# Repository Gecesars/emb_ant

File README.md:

# Painel setorial P1H · 5,09 a 5,25 GHz

**P2M19 R09 — simulações suspensas por solicitação do usuário em 14/11.** Referência RF preservada: R08, 14 passes, 20,544 dBi e ΔS 0,010484. Resumo enviado para gecesars@gmail.com. Planejamento da rede externa e montagem mecânica preliminar concluídos, com base de alumínio e dois conectores N. Falta de memória exige registro e parada sem repetição automática. [Estado, política e comunicação](projetos/P2M19/gestao_R09/README.md).

**P2M19 R08 — passes 13 e 14 concluídos em 14/11.** Malha preservada, colunas 72 mm, refletor 146 mm, 14 núcleos, 5,17 GHz, 16 entradas iguais/em fase e sem sweep. **ΔS final 0,010484 ≤0,05**; ganho frontal total **20,544 dBi**, aberturas **H 22,491° / V 3,783°**, máximos **+0,188° / +0,048°**. VSWR ativo **1,033–1,182**; maior VSWR com demais entradas casadas **1,316**. Entre os passes 13/14, ΔG **+0,0400 dB**, ΔH **−0,0986°**, ΔV **+0,0015°**; maior diferença de E/Emax **0,00353 H / 0,01006 V**. Balanço de potência consistente e zero reparos Major/Minor. O critério completo de 0,1 dB nas nove sondas por dois passes **ainda não foi atendido**; maior variação final 0,182 dB numa direção cerca de 31 dB abaixo do ganho frontal. Executados exatamente dois passes adicionais, sem novos cálculos programados. [Relatório, HFSS, VSWR e diagramas](projetos/P2M19/continuacao_72mm_ref146_14passes/README.md).

**P2M19 R07 — passes 11 e 12 concluídos em 14/11.** Malha preservada, colunas 72 mm, refletor 146 mm, 14 núcleos, 5,17 GHz, 16 entradas iguais/em fase e sem sweep. **ΔS final 0,014268 ≤0,05**; ganho frontal total **20,475 dBi**, aberturas **H 22,683° / V 3,778°**, máximos **+0,144° / +0,039°**. VSWR ativo **1,009–1,174**; maior VSWR com demais entradas casadas **1,301**. Entre os passes 11/12, ΔG **+0,0248 dB**, ΔH **−0,0634°**, ΔV **+0,0044°**. Balanço de potência consistente e zero reparos Major/Minor. A estabilidade completa de 0,1 dB nas nove sondas por dois passes **ainda não foi confirmada**; maior variação final 0,375 dB em uma direção cerca de 31 dB abaixo do ganho frontal. Executados exatamente dois passes adicionais, sem reiniciar a malha ou programar novos cálculos. [Relatório, HFSS, VSWR e diagramas](projetos/P2M19/continuacao_72mm_ref146_12passes/README.md).

**P2M19 R06 — convergência de ΔS confirmada em 14/11.** Executados somente os passes **9 e 10**, preservando os oito anteriores, colunas de 72 mm e refletor de 146 mm. 14 núcleos, 5,17 GHz, 16 entradas de 0,0625 W / 0°, sem sweep. ΔS **0,021617 / 0,024510**, dois passes consecutivos abaixo de 0,05. Ganho frontal total **20,391 dBi**, H/V **22,761° / 3,768°**, VSWR ativo **1,054–1,221** e máximo com demais entradas casadas **1,294**. Balanço de potência consistente e zero reparos Major/Minor. **A estabilidade completa dos campos ainda não foi confirmada**: ganho frontal variou +0,122 dB no último passe; maior variação entre as nove sondas foi 0,463 dB. Nenhum passe além de dez foi executado. [Resultados, HFSS e diagramas atualizados](projetos/P2M19/continuacao_72mm_ref146_10passes/README.md).

**P2M19 R05 — dois passes adicionais concluídos em 13/11, PRELIMINAR.** Preservados a geometria de colunas a 72 mm, refletor 146 mm e os seis passes anteriores; executados somente os passes 7/8, com 14 núcleos, 5,17 GHz, 16 entradas iguais/em fase, sem sweep. Resultado: **20,101 dBi**, H **22,734°**, V **3,753°**, VSWR ativo **1,143–1,353**. **ΔS=0,05196469 >0,05: não convergiu.** Balanço de potência consistente, zero reparos Major/Minor; ganho ainda variou +0,241 dB no último passe. O acompanhamento desta execução está concluído, sem novos passes programados. [Resultados, HFSS, comparação 6/8 e diagramas](projetos/P2M19/continuacao_72mm_ref146_8passes/README.md).

**P2M19 — comparação de 72/88 mm e três refletores concluída em 13/11, PRELIMINAR.** Executada fila local finita, com 14 núcleos, seis passes por geometria, entradas iguais/em fase, 5,17 GHz e sem sweep. Na comparação direta, mantendo refletor de 178 mm, colunas de 72 mm deram **19,209 dBi, H 24,238°, V 3,752°**, lóbulo horizontal **−4,866 dB** e ΔS **0,156138**. Os ajustes para refletores de 162/146 mm deram **19,418/19,500 dBi**, com H **23,989/23,550°**. **Nenhum caso convergiu ao alvo ΔS≤0,05 ou confirmou estabilidade dos campos; nenhum chegou a H=30°.** Balanços de potência consistentes, zero reparos Major/Minor, sem passes adicionais. A fila encerrou; não há agendamento recorrente. [Comparação, diagramas, nativos e evidências](projetos/P2M19/estudo_72mm/README.md) · [Operação da fila local](projetos/P2M19/automacao/README.md).

**P2M19 R01 — 16 níveis × duas colunas a 88 mm, estudo preliminar de 13/11.** Oito placas C12, 32 radiadores, dezesseis entradas de **0,0625 W / 0°**, 5,17 GHz, 14 núcleos e sem sweep. Encerrou no limite de **seis passes**, com **ΔS 0,177100 > 0,05: não convergiu**. Ganho frontal total **19,055 dBi**, abertura central H **19,428°**, V **3,820°**. Atinge 19 dBi numericamente, com margem de apenas 0,055 dB, sem validar a meta. Lóbulo horizontal em −37° a **−2,829 dB** do pico; VSWR ativo **1,364–2,295**. Balanço de potência consistente, zero reparos Major/Minor. Inclui perdas dos divisores impressos; exclui rede externa, cabos 3D e radome. [HFSS, CAD, diagramas, convergência e dados](projetos/P2M19/centro_16x2_88mm/README.md).

**P2S13 R17 — montagem DN100 dimensionada, preliminar (12/11).** Dois flanges Al Ø110 ×4,76 mm com canais **2,5 ×2,5 mm**, fixadores POM, dois N Amphenol082-6784 no flange inferior, chapa com linguetas e chicote completo. [FreeCAD, STEP, BOM, DXF e 12 páginas de documentação](projetos/P2S13/mecanica_R17/README.md). O teste sem abas resultou em **14,305 dBi, H78,77°, V10,11°, VSWR1,124/1,057**; ΔS0,030507 em seis passes, só um consecutivo válido. Abas pouco alteraram H; mantidas na montagem principal pelo vertical mais simétrico no resultado anterior. [Comparação HFSS/Nexxim e limites](projetos/P2S13/comparacao_refletor_R17/README.md). O fechamento mecânico completo ainda não foi qualificado em RF.

**P2S13 no tubo PVC — R16 concluída em 12/11 como estudo preliminar.** O ajuste `dn100_c02` atingiu **VSWR ativo 1,099 / 1,087** nas entradas do conjunto e **14,320 dBi** calculados em 5,17 GHz, com duas fontes iguais/em fase. Antena e divisor simulados separadamente; cabos somente no Nexxim, com perdas nominais. Tubo de catálogo **De 101,6 × parede 1,8 mm**, trecho aberto de 350 mm; propriedades dielétricas preliminares. Divisor convergiu em **6 passes / ΔS 0,017252**; antena encerrou em **6 / 0,041601**, sem os dois passes consecutivos exigidos e sem estabilidade completa de campos. Abertura agora informativa. **Não é qualificação do tubo comercial.** A sintonia melhora o conjunto carregado; isolado com saídas em 50 Ω, o divisor apresenta VSWR 2,154/2,153. [Pesquisa de tubos, explicação do VSWR, resultados e nativos](projetos/P2S13/tubo_pvc/README.md).

**Histórico anterior, sem tubo PVC:**

**P2S13 C09 ajustada — casamento do conjunto confirmado em 12/11.** Selecionada a c02: **VSWR ativo 1,184 / 1,226**, entradas de 0,5 W / 0° em 5,17 GHz; com a outra entrada casada, **1,142 / 1,207**. Seis ramais iguais de 19,323907 mm e PCB de 36 × 78 mm preservados, alterando apenas as duas seções dos transformadores. Divisor recalculado no HFSS: **5 passes, ΔS 0,020366, 14 núcleos**, sem radome, cabos 3D ou sweep. Nexxim efetivamente executado e conferido, erro S2 **6,15×10⁻¹⁶**. Com a antena S6 preservada, **14,146 dBi, H/V 86,241° / 10,068°, máximos 0° / +0,075°** permanecem preliminares pela estabilidade de campos da antena. O ajuste é para a carga da antena; o divisor isolado com saídas em 50 Ω tem VSWR 1,716/1,706. A abertura H≈100° e a qualificação completa continuam pendentes. [Relatório, dimensões, HFSS, Nexxim e FreeCAD](projetos/P2S13/casamento_c09/README.md). Montagem ajustada deixada aberta; nenhum novo Gerber liberado.

**Histórico C09 antes do ajuste:**

**P2S13 C09 compacto — Nexxim executado em 12/11, preliminar.** Novo divisor duplo 1:3 de **36 × 78 mm**, duas seções por ramal e comprimentos físicos/elétricos nominais iguais. HFSS separado para antena S6 e divisor S8, **sem radome e sem cabos longos em 3D**; seis coaxiais iguais de 134 mm representados por RLGC no Nexxim. Em 5,17 GHz, entradas de 0,5 W / 0°: **13,925 dBi** frontais, **VSWR 1,528 / 1,700**, H/V **86,228° / 10,073°**, máximos H/V **0° / +0,069°**. O casamento **não atende 1,25** e a abertura H está abaixo dos aproximadamente 100° buscados. Antena convergiu em **6 passes / ΔS 0,024379** e divisor em **5 / 0,019563**, todos com 14 núcleos; ainda há variação de campo de **0,309 dB** no último passe. A matriz Nexxim confere com cálculo independente, erro **4,61×10⁻¹⁶**. [Circuito nativo, diagramas, CAD e evidências](projetos/P2S13/compacto_c09/c00/README.md). Nenhum novo sweep; C08/Gerbers anteriores preservados, sem liberação C09 para fabricação.

**P2S13 R12 — continuação de oito passes e CAD/KiCad, 12/11.** Executados apenas passes 7 e 8 preservando a malha, 14 núcleos, 5,17 GHz, sem sweep e entradas 0,5 W / 0°. **ΔS 0,034291**, dois passes consecutivos ≤0,05: convergência S atendida. Ganho frontal **11,569 dBi**, VSWR ativo **1,547 / 1,455**, H/V **99,818° / 9,843°**, máximo V **−0,134°**; balanço de potência consistente. **Ganho frontal ≥12 dBi e VSWR ≤1,25 não atendidos; estabilidade de campo e simetria de 0,2 dB ainda pendentes** (assimetria V 0,208 dB). [Resultados, comparação e diagramas](projetos/P2S13/curvilinear_simplificado/continuacao8/README.md) · [KiCad/Gerbers: 3×M00 + 1×C08, DRC zero erros](projetos/P2S13/kicad/conjunto_R12/README.md) · [Montagem FreeCAD preliminar, deixada aberta](projetos/P2S13/mecanica_R12/README.md).

**Histórico P2S13 R12 — seis passes, 12/11, não validado.** Conjunto integral com C08, cabos e radome FR-4 de 2 mm; solver direto, elementos curvilíneos, 14 núcleos, duas entradas de 0,5 W / 0°. Em 5,17 GHz, seis passes: **ΔS 0,07831**, ganho frontal **11,572 dBi**, VSWR ativo **1,620 / 1,523**, H/V **98,902° / 9,796°**. O balanço de potência está consistente e o lóbulo principal vertical está praticamente centrado (**−0,008°**, assimetria **0,068 dB**). **Não atende à convergência, ao ganho frontal ≥12 dBi nem ao VSWR ≤1,25.** O pico horizontal é 12,724 dBi em +27,75°, distinto do ganho frontal. [Nativo, diagramas e auditoria R12](projetos/P2S13/curvilinear_simplificado/README.md).

**KiCad do divisor P2S13 C07 — 11/11:** [projeto, Gerbers e documentação](projetos/P2S13/kicad/divisor_duplo_1x3_C07/README.md), com a geometria nominal HFSS preservada. Conferência CAD/KiCad/CAM concluída; oito furos NPTH Ø0,9195 mm. **Fabricação padrão JLC ainda não liberada:** nove violações de folga mantidas porque o cobre chega aos furos e à borda. O ZIP inclui instruções de revisão especial; nenhum solve ou pedido de compra.

**P2S13 R09 — divisor corrigido e lóbulo principal vertical centrado nominalmente, 11/11.** Selecionada a C07, com compensação física nas trilhas e duas entradas de **0,5 W / 0°**. Em **5,17 GHz**, sem sweep: ganho frontal **12,746 dBi**, VSWR ativo **1,093/1,092**, aberturas H/V **98,614°/10,162°**, máximo vertical **−0,01°** na grade de 0,01° e assimetria máxima de **0,060 dB em ±4°**. Atende numericamente à meta atual de ≥12 dBi e à prioridade de centragem do lóbulo principal. O divisor convergiu em **seis passes**, **ΔS 0,023112**, dois consecutivos ≤0,05, **14 núcleos**, sem reparos Major/Minor; circuito conferido no Nexxim. Com a outra entrada casada, B fica em **1,255**, ligeiramente acima de 1,25. Resultado **preliminar**: permanecem as pendências de campos/reciprocidade da antena e não foi somada a radiação direta do divisor aos diagramas. [Relatório ilustrado, HFSS, FreeCAD, circuito e evidências](projetos/P2S13/divisor_duplo_1x3_correcao/README.md).

**Histórico R08, anterior à correção R09:**

**P2S13 — divisor duplo 1:3 físico simulado em 11/11.** A versão C01 concluiu seis passes, todos com 14 núcleos, em 5,17 GHz e sem sweep: **ΔS 0,049458**, dois passes consecutivos abaixo de 0,05. Conectada ao S6 da antena e conferida no Nexxim, com duas entradas de 0,5 W / 0°: **VSWR ativo 1,319/1,417**, ganho frontal **11,772 dBi**, H/V **99,308°/10,321°**. **Não atende VSWR≤1,25 nem ganho≥13 dBi.** O layout físico apresenta desequilíbrio de potência/fase nas saídas e não confirma o desempenho do plano de linhas anterior. Mantidas as ressalvas da antena e do modelo de componentes; nenhuma liberação para fabricação. [HFSS, circuito, CAD, diagramas e diagnóstico](projetos/P2S13/divisor_duplo_1x3_hfss/README.md).

**P2S13 — continuação de oito passes concluída em 11/11.** Três PCBs de dois elementos, dobra **28,5 mm / 150°**, mesma malha e geometria; somente passes 7 e 8 novos. Em 5,17 GHz, 14 núcleos, seis entradas iguais/em fase e sem sweep: **ΔS 0,017600**, ganho frontal **13,349 dBi**, H/V **98,727°/9,931°**, VSWR ativo máximo **1,3220**. Convergência S atendida; estabilidade de campos e reciprocidade estrita ainda pendentes. [Resultados e nativos](projetos/P2S13/continuacao_tres_placas2/README.md).

**Divisor duplo 1:3 — plano preliminar de circuito:** dois Wilkinson idênticos e ajuste comum de entrada resultam em VSWR máximo **1,1979** nas duas entradas, considerando fontes iguais/em fase e outra entrada casada. Ganho estimado **13,143 dBi**, H/V **98,720°/9,931°**; interconexão conferida no Nexxim. O divisor ainda não tem layout/validação EM, e os limites da malha da antena permanecem. [Plano, dimensões, dados e circuito](projetos/P2S13/divisor_duplo_1x3/README.md). [Histórico de seis passes](projetos/P2S13/tres_placas2/README.md) · [Campanha 4+2 interrompida](projetos/P2S13/dobras_placas_ajustadas/README.md).

**P2M21 R18 — mecânica PRELIMINAR concluída em 10/11:** [documentação, FreeCAD, chapa dobrada/planificada, BOM e imagens](projetos/P2M21/mecanica_preliminar_R18/README.md). Dez PCBs de quatro elementos, cinco por coluna: **20 níveis × 2 colunas**, passos **48/78 mm**, refletor de alumínio 2 mm, grampos de POM e dois N Amphenol 082-6784 a partir do STEP fornecido. Cabos de referência UT-141C. **Simulações interrompidas a pedido do usuário; nenhum solver será retomado automaticamente.** A rede externa de duas entradas para vinte conexões permanece pendente, assim como a liberação RF/mecânica. [Histórico R15/R16 e interrupção R17](projetos/P2M21/comparacao_colunas_niveis/README.md).

**P2M21, oito placas `4_elementos` — R14 de 10/11:** [conjunto 16×2, resultados e comparação](projetos/P2M21/oito_celulas_4_elementos/README.md), com passo horizontal aprovado de **72 mm** e folga de **2 mm**. Ensaio central com 16 portas iguais/em fase: **18,88 dBi**, H **25,25°**, V **3,75°** e VSWR ativo máximo **1,842**. **Ainda não validado: seis passes, ΔS 0,16430; requisito mantido em 0,05.** Nativos HFSS/FreeCAD, S16 e diagramas preservados, sem malhas no Git. Rede externa pendente da validação; sem sweep; a continuação posterior está registrada na R15.

**KiCad 4_elementos — 10/11:** [placa e documentação](projetos/P2M21/kicad/4_elementos/README.md) · [Gerbers para JLCPCB](projetos/P2M21/kicad/4_elementos/4_elementos_gerbers_JLCPCB.zip). Geometria R13 C12 preservada, 70 × 184 mm, RO4350B de núcleo 0,76 mm, dois divisores 1:4; DRC sem erros ou desconexões. O apontamento H +0,75° ainda excede a tolerância atual de ±0,5°; V −0,25° atende.

**P2M21 — módulo de quatro elementos, R13 de 10/11:** casamento numérico **VSWR ≤1,25 em 5,09–5,25 GHz**, com Fast de 161 pontos e conferências discretas. Pior VSWR ativo **1,23548**, outra entrada casada **1,23260**. Em 5,17 GHz: **12,4566 dBi**, H **72,055°**, V **15,183°**; máximos **+0,75°/−0,25°**, mantendo a ressalva de apontamento horizontal. Seis passes, ΔS **1,672%**, 14 núcleos, entradas iguais/em fase e cabos físicos com perdas. [Relatório, curvas, dimensões e nativos](projetos/P2M21/quatro_elementos_casamento_banda/README.md). A aprovação do casamento deste módulo não qualifica o painel completo de 21 dBi.

**P1H semipronta — campanha R07 suspensa a pedido do usuário em 8/11.** A R06 permanece qualificada somente em 5,17 GHz. O centro R07 foi conferido; a varredura de 17 frequências foi interrompida voluntariamente para iniciar o novo projeto. Não há aprovação de banda R07. [Registro do congelamento](resultados/r07/estado_semipronta.json).

**Continuação central P2M21 concluída:** dois passes adicionais, seis no total, em 5,17 GHz; 14 núcleos nos passes finais. Ganho total **23,32 dBi**, H **32,54°**, V **3,48°**. **Preliminar: ΔS 0,110424, sem convergência e com reprovações numéricas.** Sem sweep. [Comparação e diagramas polares E/Emax](projetos/P2M21/centro_sem_refinamento/continuacao_6_passes/README.md) · [Histórico de quatro passes](projetos/P2M21/centro_sem_refinamento/README.md).

**Novo projeto P2M21:** duas colunas, 16 níveis e duas entradas MIMO independentes, com meta de **21 dBi por entrada em 5,09–5,25 GHz**, a outra entrada casada em 50 Ω. [Concepção, placas KiCad, montagem FreeCAD e HFSS separado](projetos/P2M21/README.md).

**R06 qualificada numericamente em 5,17 GHz:** PCB contínua de dez elementos com divisores compactos, duas entradas de 0,5 W a 0°, cabos ideais sem atenuação. Resultado final: **17,3593 dBi, H 96,0643°, V 5,6158°**, VSWR ativo A/B **1,2115 / 1,1292** e com a outra entrada casada **1,2321 / 1,2474**. Convergência de 23 passes, estabilidade de malha aprovada e circuito conferido no Nexxim. [Relatório ilustrado de 15 páginas](resultados/r06/P1H_R06_Relatorio.pdf) · [Resultados e limites](resultados/r06/README.md) · [Cotação JLCPCB](resultados/r06/cotacao.md) · [Montagem e chapa R06](freecad/mecanica_R06/README.md). O aceite é somente no centro da banda, sem perdas dos cabos e com conectores N ideais. Os resultados reprovados abaixo são históricos, sob o método anterior.

**Histórico R02 — cálculo integrado anterior.** As duas montagens com divisores compactos reprovam o requisito conjunto de abertura horizontal e ganho em toda a banda. A 5,17 GHz, a placa contínua produziu **94,82° / 5,54° / 12,00 dBi** e as dez placas individuais **105,13° / 5,57° / 13,48 dBi**, respectivamente em H, V e ganho frontal realizado. A compacta teve a menor perda de distribuição entre as arquiteturas estudadas. [Comparação dos painéis](resultados/r02/comparacao_paineis.md) · [Relatório de engenharia](resultados/r02/Relatorio_P1H.pdf) · [Quatro materiais e divisores alongados](resultados/r03/README.md)

Projeto de uma coluna de dez antenas impressas com duas polarizações e passo de 52,6 mm no eixo X. A comparação atual usa duas PCBs distribuidoras, uma para os cinco radiadores inferiores e outra para os cinco superiores. Cada PCB atende às duas polarizações. A referência de ganho é a potência incidente nas duas entradas N, com 0,5 W a 0° em cada uma. Os modelos anteriores com divisor único e ramais de 254 mm também estão preservados.

| Para consultar | Arquivos |
|---|---|
| Modelos HFSS das duas montagens | [Uma placa](hfss/antenas/P1H_Continua.aedt) · [Dez placas](hfss/antenas/P1H_Separadas.aedt) · [Elemento de origem](hfss/antenas/P1H_AB_em_fase.aedt) |
| Modelos HFSS da alimentação | [Divisor de 22 portas](hfss/alimentacao/Divisor_2x10_PTFE.aedt) · [Transição soldada](hfss/alimentacao/Junta_UT141_P1H.aedt) |
| Fontes KiCad | [Coluna contínua](kicad/P1H_Coluna_10) · [Radiador individual](kicad/P1H_Individual) · [Divisor duplo](kicad/Divisor_2x10) |
| Referências dimensionais FreeCAD | [Uma placa](freecad/P1H_10_Continua.FCStd) · [Dez placas](freecad/P1H_10_Separadas.FCStd) · [Envelope do divisor](freecad/Divisor_2x10_PTFE.FCStd) |
| Mecânica do protótipo com refletor contínuo | [Montagem, chapa dobrada, planificação e desenho de fabricação](freecad/mecanica_R01/README.md) |
| Painel integrado R01 | [Modelo HFSS com duas portas N](hfss/antenas/P1H_R01.aedt) · [Premissas e reprodução](automacao/r01/README.md) · [Cotação da placa contínua e do divisor](resultados/r01/cotacao.md) |
| R02 com divisores inferior e superior | [Montagem, chapa e chicote](freecad/mecanica_R02/README.md) · [HFSS integrado](hfss/antenas/P1H_R02.aedt) · [Reprodução](automacao/r02/README.md) · [Cotação das três placas](resultados/r02/cotacao.md) |
| Controle R02-S com as dez placas individuais | [HFSS no mesmo refletor e rede R02](hfss/antenas/P1H_R02_10Separadas.aedt) · [Comparação convergida dos painéis](resultados/r02/comparacao_paineis.md) · [Comparação dos divisores em 50 Ω](resultados/r02/rede/README.md) · [Relatório de engenharia](resultados/r02/Relatorio_P1H.pdf) |
| R03 com saídas alinhadas e dois divisores alongados | [Comparação com a compacta e quatro laminados](resultados/r03/README.md) · [Montagem e chapa](freecad/mecanica_R03/README.md) · [HFSS do painel completo](hfss/antenas/P1H_R03_Alongada.aedt) · [Cotação](resultados/r03/cotacao.md) |
| Fabricação | [Pacotes Gerber com furação das revisões](fabricacao/gerbers) · [Ligação dos cabos da versão inicial](fabricacao/montagem/ligacao_dos_cabos.csv) · [Cotação JLCPCB inicial](fabricacao/cotacao/Cotacao_JLCPCB.md) |
| Estudos anteriores | [Colunas de 8, 9 e 10 elementos](documentacao/historico/comparacao_colunas.md) · [Elemento com ambas as portas em fase](documentacao/historico/analise_AB.md) · [Dados numéricos](resultados/historico) |
| Como reproduzir | [Procedimento e convenções](automacao/README.md) |

Os **critérios atuais de RF da R06** são abertura horizontal a −3 dB entre 81° e 99° (alvo 90°), VSWR < 1,5 nas duas entradas e ganho realizado frontal ≥ 16 dBi em +Z, no centro de 5,17 GHz e sem perdas dos cabos. A abertura vertical pode ser menor que 7°. A banda de interesse continua 5,09–5,25 GHz; os 17 pontos dos divisores não demonstram por si só desempenho do painel em toda a banda. As reprovações dos painéis integrais anteriores permanecem como histórico.

O ensaio anterior das duas revisões de PCB com refletores individuais foi interrompido após a convergência da placa contínua no centro da banda. O ganho mínimo de 16,58 dBi do estudo histórico corresponde às antenas individuais antes dos ajustes dos pads e furos. As campanhas R01, R02 e R02-S usam a mecânica completa, incluindo o refletor dobrado e os conectores N. [Estudo histórico](documentacao/historico/comparacao_colunas.md)

No painel completo R01, o ponto convergido de 5,17 GHz apresentou 14,06 dBi de ganho frontal e aberturas de 102,34° na horizontal e 6,19° na vertical. A R01 reprova as metas simultâneas de banda. [Campos, convergência e métricas](resultados/r01/README.md)

Os **radiadores** usam RO4350B de 0,76 mm (Dk de projeto 3,66). Os divisores de referência usam PTFE ZYF300CA-C de 1,52 mm. São espessuras do laminado. A placa longa mede 501,7125 × 28,3125 mm e a individual mede 28,3125 × 28,3125 mm. Os modelos RF anteriores usam dez refletores individuais de 48,3125 × 36 mm. Os protótipos mecânicos R01 a R03 usam refletor contínuo dobrado de alumínio de 2 mm, apoios em poliacetal e conectores N com junta de vedação. Os modelos históricos de cobre excluíam a camada de níquel-fósforo; a R06 inclui ENIG nominal sobre cobre físico de 35 µm.

Os modelos HFSS nativos podem gerar a malha novamente. O Git guarda projetos, dados de engenharia e documentos. As malhas, os campos volumétricos, os backups e os arquivos temporários ficam nos diretórios locais de trabalho. Os Gerbers em **fabricacao/gerbers** correspondem aos protótipos cotados. As campanhas integrais anteriores reprovam suas metas; a R06 atende ao aceite de centro pelo método separado solicitado, conforme o relatório final.

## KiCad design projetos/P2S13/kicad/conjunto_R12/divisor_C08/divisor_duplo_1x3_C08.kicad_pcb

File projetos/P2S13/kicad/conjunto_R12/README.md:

# Conjunto R12 no KiCad — três placas M00 e divisor C08

Pacote de 12/11/2026 com **três placas radiantes idênticas de dois elementos M00** e **um divisor duplo 1:3 C08**. São quatro PCBs, seis elementos radiantes e seis interligações coaxiais de 50 mm. As duas entradas externas pertencem à C08; cada polarização alimenta uma das entradas das três M00.

**Geometria nominal simulada preservada. A qualificação RF é separada e este pacote não libera produção.** A R12 com radome está em verificação de convergência; consultar [resultados R12](../../curvilinear_simplificado/README.md) e sua continuação. Não foi alterado cobre para corrigir casamento, DRC ou adaptação de processo.

| PCB | Quantidade por antena | Arquivo editável | Gerbers |
| --- | ---: | --- | --- |
| Radiante M00, dois elementos e dois divisores 1:2 | 3 | [2_elementos.kicad_pro](placa2_M00/2_elementos.kicad_pro), [PCB](placa2_M00/2_elementos.kicad_pcb) | [M00 — para revisão RF/processo](placa2_M00/M00_Gerbers_PARA_REVISAO_RF.zip) |
| Divisor duplo 1:3 C08 | 1 | [divisor_duplo_1x3_C08.kicad_pro](divisor_C08/divisor_duplo_1x3_C08.kicad_pro), [PCB](divisor_C08/divisor_duplo_1x3_C08.kicad_pcb) | [C08 — pacote original preservado](divisor_C08/C08_Gerbers_PARA_REVISAO_RF.zip) |

A M00 foi criada agora no KiCad 10.0.5 a partir da arte exata usada no HFSS. A placa antiga `projetos/P2M21/kicad/2_elementos` é uma versão v05 diferente e foi preservada. A C08 já existia e foi reutilizada byte a byte, incluindo suas conferências; não houve redesenho.

## Especificações nominais

| Item | M00 | C08 |
| --- | --- | --- |
| Dimensões | 50 × 88 mm | 220 × 64 mm |
| Núcleo dielétrico | RO4350B, 0,76 mm | ZYF300CA-C, 1,52 mm |
| Valores usados no HFSS | εr 3,66; tanδ 0,0037 | εr 2,94; tanδ 0,0016 |
| Cobre externo | 35 µm por face | 35 µm por face |
| Espessura geométrica núcleo+cobre | 0,83 mm, antes do acabamento | 1,59 mm, antes do acabamento |
| Acabamento | ENIG nominal, sem máscara e sem serigrafia | ENIG nominal, sem máscara e sem serigrafia |
| Furos acabados por placa | 4 vias Ø0,40 mm + 2 entradas Ø1,10 mm, todos PTH | 8 entradas/saídas Ø1,10 mm, todos PTH |
| Diâmetro nominal das ilhas | Vias Ø0,726 mm; pads PTH Ø1,60 mm, com cobre superior de entrada Ø1,90 mm incorporado à arte | Ø1,80 mm |
| Metalização de parede no modelo RF | **35 µm** | **18 µm** |
| NPTH / componentes SMD | Nenhum | Nenhum |

O acabamento ENIG do modelo usa Au 0,0254 µm e NiP 4,5 µm nominal. As espessuras de parede dos PTH foram lidas dos sólidos do CAD; não são suposições do exportador KiCad. Em especial, **não substituir os 35 µm de metalização da M00 pelos 18 µm da C08 sem revisão de engenharia**. As notas preservam o modelo, mas disponibilidade, tolerâncias finais e stackup precisam ser confirmados com o fabricante antes da compra. Não houve cotação ou pedido nesta entrega.

Na M00, o passo dos elementos é 48 mm; transformadores de sinal medem 0,546717 mm de largura × 13,151813 mm de comprimento. O sinal de 50 Ω tem largura 1,623415 mm. As entradas ficam em HFSS X=2,509168413 mm, Y=−18 mm (A) e +18 mm (B). Os planos de retorno e divisores acrescentados são simétricos, mantendo as transições dos radiadores originais.

## Conferências

- M00: **zero erros DRC e zero itens desconectados**. Os 138 avisos são de pontes de máscara porque a abertura cobre toda a PCB; não há exclusões DRC para ocultá-los.
- C08: DRC repetido em 12/11, **zero erros e zero desconectados**, com 113 avisos do mesmo tipo. Todos os 18 arquivos originais do pacote foram comparados por SHA-256.
- Cobre KiCad M00 comparado à arte efetiva, incluindo anilhas, pads e furos: desvio máximo de 0,000001 mm nas bordas. Conferência independente com as 14 faces de cobre do CAD FreeCAD usado na R12: tolerância de 0,000005 mm, dez grupos camada/rede.
- Gerbers X2 e Excellon realmente exportados foram relidos e comparados. Contorno fechado, máscara integral, cobre e furação corretos. Furação em formato 3:6 mm, resolução nominal 0,000001 mm; erro máximo de arredondamento XY de 0,000000878 mm. Esses números são precisão digital de exportação, **não tolerâncias de fabricação**.
- Continuidade das redes SIG_A, SIG_B, RET_A e RET_B verificada, sem curto entre redes. Folga mínima entre redes da M00: 0,188750 mm; cobre a 4 mm da borda.

Evidências: [conferência CAD do conjunto](conferencia_CAD_conjunto.json), [M00 KiCad](placa2_M00/verificacao.json), [M00 CAM](placa2_M00/verificacao_gerbers.json), [C08](divisor_C08/verificacao.json), [origem C08](origem_C08.json) e [manifesto](manifesto.json).

## Montagem e reprodução

Centros das três placas radiantes no conjunto: X=−96, 0 e +96 mm. Entre bordas há 8 mm de vão. Divisor C08 com giro de 180° em X e translação Z=−35,231 mm conforme a configuração HFSS; não espelhar Gerbers para obter essa orientação de montagem. Ver [lista de placas](lista_placas.csv) e [interligações](interligacoes.csv).

Os projetos contêm objetos KiCad editáveis: polígonos de cobre associados a redes, pads PTH, vias, contorno e stackup. Não foram criados componentes fictícios nem um esquema lumped para substituir a geometria distribuída RF. Identificações estão em F.Fab e não são enviadas como serigrafia. Não há BOM/CPL de montagem automática; os cabos são soldados manualmente.

Os scripts `r12_kicad_preparar.py`, `r12_kicad_placa2.py`, `r12_kicad_furacao.py`, `r12_kicad_conferir.py`, `r12_kicad_gerbers.py`, `r12_kicad_faces_cad.py` e `r12_kicad_validar_cad.py` em `projetos/P2S13/automacao` reproduzem geração e auditoria sem executar HFSS. Preservar os arquivos-fonte, as notas de fabricação e a revisão antes de regenerar o pacote.

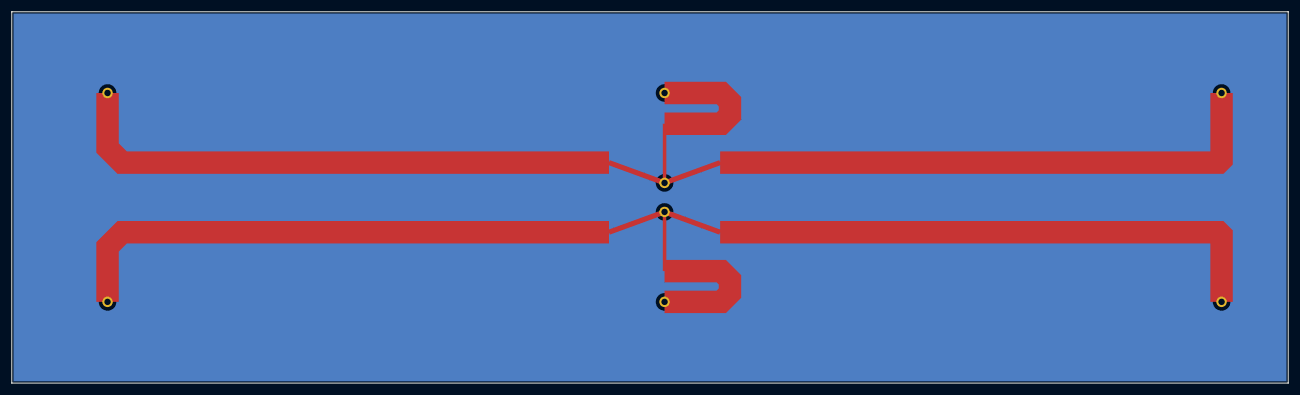
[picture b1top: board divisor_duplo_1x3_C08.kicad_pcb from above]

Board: 2 copper layers, 220.0 x 64.0 mm, 8 parts (0 on the bottom side), 3 nets, no tracks yet.

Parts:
J1: IN_A_COAX_SOLDADO
J2: R1_A_COAX_SOLDADO
J3: R2_A_COAX_SOLDADO
J4: R3_A_COAX_SOLDADO
J5: IN_B_COAX_SOLDADO
J6: R1_B_COAX_SOLDADO
J7: R2_B_COAX_SOLDADO
J8: R3_B_COAX_SOLDADO

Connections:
GND: J1.2, J2.2, J3.2, J4.2, J5.2, J6.2, J7.2, J8.2
SIG_A: J1.1, J2.1, J3.1, J4.1
SIG_B: J5.1, J6.1, J7.1, J8.1

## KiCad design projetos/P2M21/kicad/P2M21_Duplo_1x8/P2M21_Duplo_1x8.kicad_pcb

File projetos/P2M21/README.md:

# P2M21 — duas colunas, MIMO 2×2, meta de 21 dBi por entrada

**P2M21 R18 — mecânica PRELIMINAR concluída em 10/11:** [documentação, FreeCAD, chapa dobrada/planificada, BOM e imagens](mecanica_preliminar_R18/README.md). Dez PCBs de quatro elementos, cinco por coluna: **20 níveis × 2 colunas**, passos **48/78 mm**, refletor de alumínio 2 mm, grampos de POM e dois N Amphenol 082-6784 a partir do STEP fornecido. Cabos de referência UT-141C. **Simulações interrompidas a pedido do usuário; nenhum solver será retomado automaticamente.** A rede externa de duas entradas para vinte conexões permanece pendente, assim como a liberação RF/mecânica. [Histórico R15/R16 e interrupção R17](comparacao_colunas_niveis/README.md).

**Painel de oito células — R14 de 10/11:** [montagem HFSS/FreeCAD, diagramas e comparação](oito_celulas_4_elementos/README.md). Oito cópias de `4_elementos`, em quatro placas verticais × duas colunas, totalizam 16 níveis × 2 radiadores. Passos de **48 mm vertical / 72 mm horizontal**, com **2 mm de folga lateral**. Em 5,17 GHz, 16 portas de 0,0625 W/0°, 1 W total: **18,8776 dBi**, H **25,2549°**, V **3,7541°**, máximos **−1,25° / 0°**, VSWR ativo máximo **1,8421** e com demais portas casadas **1,4125**. **Não validado: seis passes, ΔS 0,164297, acima do alvo 0,05**, e campos ainda variando. Malha sem reparos Major/Minor; passividade, reciprocidade e recomposição dos campos conferidas. Mantidos 14 núcleos, sem GUI e sem sweep; inclui os cabos físicos de 50 mm das células. O painel individual R04 também não convergiu e tem outros espaçamentos, portanto a comparação é histórica. A rede externa de duas entradas para 16 conexões aguarda validação dos diagramas; o estado de seis passes é histórico; os dois passes adicionais autorizados estão registrados na R15.

**KiCad em 10/11 — [4_elementos](kicad/4_elementos/README.md):** criada a placa de **70 × 184 mm**, com passo de **48 mm** e dois divisores 1:4, preservando a geometria R13 C12. [Gerbers/Excellon para JLCPCB](kicad/4_elementos/4_elementos_gerbers_JLCPCB.zip), RO4350B de núcleo 0,76 mm. Cobre, contorno e dez furos conferidos; **DRC sem erros ou desconexões**. A tolerância atual é **±0,5° em H e V**: a C12 mantém H +0,75° (fora) e V −0,25° (dentro). Esta conversão não altera a geometria nem inicia nova simulação.

**Módulo de quatro elementos — R13 concluída em 10/11:** a meta de **VSWR ≤1,25** foi atendida numericamente na banda de **5,09–5,25 GHz**. O Fast tem 161 pontos de saída e foi conferido por soluções discretas em 5,09/5,17/5,25 GHz e no pior ponto, **5,173 GHz**. Máximo ativo confirmado: **1,23548**; com a outra entrada em 50 Ω: **1,23260**. O ajuste usa três seções nos transformadores de raiz, iguais nas duas polarizações, mantendo os dipolos, passo de **48 mm** e altura de **14,949 mm**. [Relatório, dimensões, curvas, HFSS e FreeCAD](quatro_elementos_casamento_banda/README.md).

Em **5,17 GHz**, A=B=0,5 W/0°: **12,4566 dBi frontais**, aberturas **H 72,055° / V 15,183°**, máximos **H +0,75° / V −0,25°** e SLL vertical **−10,075 dB**. A forma e as larguras foram preservadas nos limites documentados; o máximo horizontal ainda excede o limite de trabalho de ±0,5°. Portanto, o casamento atende à meta, com essa ressalva de apontamento. **Seis passes, convergida em ΔS 1,672%, 14 núcleos**, sem novos passes nos sweeps. Inclui os dois cabos físicos de 50 mm e suas perdas. Ganho e diagramas foram calculados somente no centro; esta entrega não qualifica o painel 16×2 ou o desempenho MIMO por entrada.

**Módulo de quatro elementos — continuação R12 de 9/11:** [oito passes e Fast da banda](quatro_elementos_8passes_fast/README.md). A variante com passo de **48 mm** e altura de **14,949 mm** recebeu exatamente os passes 7 e 8, preservando a malha anterior. **Convergiu**, com ΔS final **1,977%**, dois passes consecutivos abaixo de 5% e 14 núcleos. Em **5,17 GHz**, com A=B=0,5 W/0°: **12,7586 dBi frontais**, VSWR ativo **1,3648/1,2285**, casado **1,2091/1,1733**, aberturas **H 73,322° / V 15,058°**, máximos **H 0° / V −1,25°** e SLL vertical **−9,095 dB**. O **Fast de 5,09–5,25 GHz**, com 161 pontos de saída e sem novos passes adaptativos, revelou máximos de VSWR ativo **2,2796/2,0142 em 5,09 GHz**. Portanto, a convergência foi atingida, mas o casamento na banda e o apontamento vertical ainda precisam de ajuste. Ganho e diagramas foram medidos somente no centro. A referência R11 permanece preservada; o ajuste de casamento R13 esta documentado acima.

**R00: concepção criada, ainda sem qualificação eletromagnética do novo painel.** A P1H foi preservada como semipronta; seus resultados não aprovam esta nova geometria.

**Distribuição solicitada em 9/11:** [dez divisores 1:4 em cinco PCBs duplas](rede_dez_1x4/README.md), com dois circuitos centrais e oito locais. O usuário aprovou uma entrada por polarização e as divisões finais 1:2 impressas nas placas radiantes. A integração do painel completo continua pendente; os estudos de módulos usam dois ou quatro elementos verticais e dois cabos físicos.

**Estudo do módulo de dois elementos:** foram testadas conexões centrais, retornos de terra e comprimentos dos divisores impressos, em 5,17 GHz, na GUI, com 14 núcleos e até seis passes por geometria. A comparação distingue apontamento, casamento e convergência e mantém a referência original. [Resultados, diagramas e nativos das variantes](dois_verticais_divisor/README.md). Este módulo não qualifica o painel 16×2 nem a banda MIMO.

**KiCad e expansão em 9/11:** criada a placa [2_elementos](kicad/2_elementos/README.md) a partir da v05 convergida, com 49 × 82,8 mm, DRC sem erros ou conexões pendentes e comparação geométrica com a fonte HFSS. O [planejamento de quatro elementos verticais](planejamento/4_elementos/README.md) foi convertido no ensaio HFSS abaixo, mantendo passo de 48 mm, duas conexões centrais e um divisor 1:4 por polarização, em uma placa de 70 × 178,8 mm.

**Quatro elementos — ajuste R11 de 9/11:** [comparação de divisores, espaçamentos e distância ao refletor](quatro_elementos_ajuste/README.md). Foram preservados 19 ensaios em 5,17 GHz, incluindo passos de 42/44/48/50/52/54 mm e distâncias de 14,949/16,610/18,271 mm. As variantes finais mantêm divisores espelhados e duas entradas de 0,5 W / 0°. O candidato numérico mais promissor usa **48 mm de passo e 14,949 mm entre laminado e refletor**, com transformadores de raiz iguais de **0,656371 × 9,000142 mm**: **12,7018 dBi frontais**, VSWR ativo **1,2327/1,0940**, casado **1,1041/1,1808**, aberturas **H 73,630° / V 15,180°** e SLL vertical **−8,385 dB**. Continua **preliminar, não liberado**: seis passes, **ΔS 0,057225 (5,7225%)**, acima do alvo de 5%, e máximos **H −1,00° / V −1,25°**. Nenhum ensaio R11 completou os dois passes consecutivos de convergência configurados. O estudo usa 14 núcleos, sem GUI, sem sweep, com os dois cabos físicos de 50 mm e perdas nominais; não qualifica o painel 16×2. A comparação controlada de alturas foi preservada separadamente do reajuste posterior do transformador.

**Quatro elementos — referência R10 de 9/11:** [modelo, resultados e diagramas](quatro_elementos_hfss/README.md). Simulação sem GUI, 14 núcleos, somente 5,17 GHz, dois divisores 1:4 impressos e dois cabos físicos de 50 mm, fontes de 0,5 W / 0° cada. Terminou no limite de seis passes com **ΔS = 0,048783 (4,8783%)**, acima do alvo de 4%: **preliminar, não convergido**. Ganho frontal realizado total **11,0946 dBi**; VSWR ativo A/B **1,4470 / 1,5774**. Máximos dos cortes H/V em **−25,25° / +0,50°**, com aberturas **83,858° / 14,961°**. A frente está 0,404 dB abaixo do pico horizontal; o pico não está centrado em 0° e a entrada B excede VSWR 1,5. Malha sem reparos Major/Minor, matriz passiva e balanço de potência conferido; essas verificações não substituem a convergência. Não foi executado sweep nem ampliado o limite de passes.

**Continuação concluída em 9/11:** somente os dois passes adicionais autorizados (5 e 6), mantendo 14 núcleos e 5,17 GHz. Resultado: **23,3227 dBi, H 32,5429°, V 3,4843° e ΔS 0,110424**. Continua **preliminar e não convergido**; a eficiência calculada de 100,425% e o erro de reciprocidade também impedem a qualificação. Os dois diagramas polares E/Emax foram revisados visualmente. [Comparação, dados e diagramas](centro_sem_refinamento/continuacao_6_passes/README.md).

**Histórico do painel completo — 9/11:** somente ganho total e diagramas H/V em **5,17 GHz**, com 16 níveis × 2 colunas e as 64 portas iguais/em fase. A revisão R04 usa Classic com resolução global padrão, sem refinamentos locais/iniciais impostos, sem lambda refinement inicial e com base mista. O primeiro cálculo foi limitado a quatro passes; o pedido seguinte autorizou exatamente mais dois, preservando a malha e o histórico. A continuação terminou às 05:53 com **seis passes no total**, sem sweep e sem alteração geométrica. O resultado de quatro passes permanece arquivado: **23,06 dBi, H 32,72°, V 3,50° e ΔS 0,617681**. [Histórico de quatro passes](centro_sem_refinamento/README.md). O ensaio R02 e a tentativa TAU R03 permanecem históricos. A alimentação direta não inclui a rede externa nem comprova ganho MIMO por entrada.

**Estudo de 9/11, antes de corrigir a malha:** a pedido do usuário, foi comparada a alimentação de **todas as portas A/B simultaneamente, com amplitude igual e fase de 0°**, mantendo 1 W total. A estimativa com a referência P1H R06 favorece manter **16 níveis × 2 colunas**: ganho total frontal de aproximadamente **22,50 dBi**, H **39,1°** e V **3,49°** em 5,17 GHz, sem a nova rede. O caso 10×2 fica em 20,46 dBi. Foram documentadas 36 combinações de níveis, colunas e espaçamentos. Este estudo coerente não comprova o requisito MIMO por entrada nem a banda e não alterou a geometria ou iniciou novo ciclo HFSS. [Comparação, método e gráficos](estimativa_uniforme/README.md).

**Atualização de 8/11, após a execução R00:** a antena terminou às 16h43 sem convergir em seis passes: ΔS = 0,040859, contra o limite então adotado de 0,02. Foram identificados sete corpos com reparos Major. Aquela fila interrompeu antes da varredura do painel e do circuito; ganho e VSWR por entrada nos 17 pontos continuam sem confirmação. [Diagnóstico e evidências](diagnostico_20261108.md).

O requisito original do projeto, ainda não qualificado e fora desta etapa de centro, é ganho frontal realizado **≥21 dBi em cada entrada**, de **5,09 a 5,25 GHz**, nos 17 pontos separados por 10 MHz, com a outra entrada terminada em 50 Ω. Cada entrada alimenta uma polarização dos 32 radiadores, distribuídos nas duas colunas. Os dois canais permanecem independentes. Não se soma a potência dos canais para alegar 21 dBi por entrada.

## Arquitetura escolhida

| Item | R00 |
|---|---|
| Arranjo | 16 níveis × 2 colunas; 32 radiadores de duas polarizações |
| Passo vertical / horizontal | 52,6 / 40 mm |
| Placas radiantes | 4 módulos iguais de 2 colunas × 4 níveis |
| Dimensão de cada módulo | 186,1125 × 68,3125 mm |
| Radiadores | RO4350B, núcleo 0,76 mm; Dk de projeto 3,66; tanδ 0,0037 |
| Alimentação | Um divisor duplo 1:4 central e quatro divisores duplos 1:8 locais |
| Placa de cada divisor | 39 × 78 mm, PTFE ZYF300CA-C de 1,52 mm; Dk 2,94; tanδ 0,0016 |
| Metalização RF | Cu físico 35 µm; ENIG nominal Au 0,0254 µm / NiP 4,5 µm |
| Refletor | Face 850 × 100 mm; alumínio 2 mm; base dobrada a 90° |
| Apoios | Oito berços transversais em poliacetal, espessura 5 mm |
| Entradas mecânicas | Dois furos Ø16 mm na base, reservados aos conectores N |

RO4350B é laminado hidrocarboneto/cerâmico; o PTFE está nas distribuidoras. A disponibilidade dessas famílias e espessuras foi consultada no contexto P1H: [materiais JLCPCB](https://jlcpcb.com/news/rogers-ptfe-high-frequency-pcb-available). A cotação P1H não é uma cotação destas novas placas. Não houve compra.

[Detalhe do cobre nas duas faces da PCB](imagens/pcb_duas_faces.png)

## Por que 16 níveis e distribuição central

Foram comparados 10, 12, 14, 16, 18 e 20 níveis, com separações entre colunas de 32 a 48 mm. O pré-dimensionamento usa os campos complexos **por entrada individual** da R06 em 5,17 GHz, escala de número de radiadores e fator de arranjo horizontal. A seleção 16×2/40 mm dá uma estimativa de **22,42 dBi antes da reserva adicional**, ou **21,67 dBi com reserva de projeto assumida de 0,75 dB**, H aproximadamente **37,85°** e V aproximadamente **3,57°** no centro. A reserva não é perda simulada nem comprovação de banda. O novo acoplamento, as emendas das PCBs, o refletor e a rede podem alterar esses valores.

[Tabela de alternativas](planejamento/comparacao.csv) · [Gráfico](planejamento/predimensionamento.png) · [Premissas e referência](configuracao.json)

As distribuidoras locais ficam atrás dos centros dos quatro módulos, em X = −315,6, −105,2, +105,2 e +315,6 mm. A raiz fica em X = 0. Isso reduz a maior distância longitudinal entre centros, de 740,6 mm para uma raiz na base a 315,6 mm para a raiz central. Trata-se de comparação geométrica, antes dos arcos e conexões.

O histórico P1H mostrou perdas e desequilíbrios maiores nas versões alongadas inicialmente testadas. Por isso esta R00 parte de distribuidoras compactas locais. As redes são divisores radiais com transformadores de quarto de onda: **não são Wilkinson e não têm resistores de isolamento entre as saídas da mesma polarização**. O circuito completo deve considerar as reflexões e o acoplamento dos radiadores.

O [mapa de conexões](mapa_conexoes.csv) associa as 64 portas dos radiadores às saídas dos divisores. A atribuição minimiza a soma das distâncias ortogonais. Há reservas iniciais iguais de **165 mm nos ramais** e **365 mm nos troncos**, calculadas com margem para roteamento. **Não são comprimentos de corte liberados:** faltam as curvas físicas, folgas de montagem e o ajuste das fases usando as matrizes S reais. As entradas N na base exigem duas ligações adicionais até a raiz. A montagem CAD ainda não inclui o chicote e os conectores N detalhados.

## Arquivos criados

- [Módulo radiante KiCad](kicad/P2M21_Modulo_2x4/P2M21_Modulo_2x4.kicad_pcb), [divisor duplo 1:4](kicad/P2M21_Duplo_1x4/P2M21_Duplo_1x4.kicad_pcb) e [divisor duplo 1:8](kicad/P2M21_Duplo_1x8/P2M21_Duplo_1x8.kicad_pcb).
- [Montagem FreeCAD](freecad/P2M21_Montagem.FCStd), [chapa dobrada STEP](freecad/Refletor_dobrado.step), [planificação FreeCAD](freecad/Refletor_planificado.FCStd) e [DXF de corte/dobra](freecad/Refletor_corte_dobra_R00.dxf).
- HFSS separado: [antena de 64 portas](hfss/antena/P2M21_Antena.aedt), [divisor de 10 portas](hfss/divisor_1x4/P2M21_Duplo_1x4.aedt) e [divisor de 18 portas](hfss/divisor_1x8/P2M21_Duplo_1x8.aedt).

O cobre do radiador foi copiado do CAD R06, incluindo vias e soldas locais; os substratos, distribuição em duas colunas, reflector e apoios são novos. Os scripts em [automacao](automacao) reproduzem a construção. O CAD nativo mantém os corpos separados para edição e posicionamento; não recupera uma árvore de esboços do cobre importado. A montagem é por posicionamento, não uma montagem cinemática.

## Verificações e limites

O primeiro ensaio do divisor duplo 1:4 convergiu em seis passes, com ΔS final 0,01449 e dois passes consecutivos aprovados. Em 5,17 GHz, com todas as saídas casadas, VSWR A/B = 1,53665 / 1,53646; perda excedente = 0,33193 / 0,33038 dB. Isso ainda não aprova o casamento nem o ganho do painel carregado. A fila inicial resolve os divisores em separado e só então o centro da antena, sem aumentar o limite de seis passes. O estado de execução está em [qualificacao.json](qualificacao.json).

O divisor duplo 1:8 também convergiu em seis passes, com ΔS 0,018707 e dois consecutivos aprovados. No centro, VSWR A/B = 1,69614 / 1,69673 e perda excedente = 0,52494 / 0,52296 dB. As terminações casadas desse ensaio não reproduzem a impedância ativa da antena; o casamento final depende do circuito carregado. **Ambos completaram os 17 pontos**, com passividade/reciprocidade verificadas e zero reparos Major/Minor. A execução da antena de 64 portas ocorreu em 8/11 das 16:03 às 16:43 e terminou sem convergência; ainda não há ganho qualificado do painel.

Os modelos CAD foram reabertos e verificados: 653 objetos na antena, 44 no divisor 1:4 e 76 no 1:8, todos válidos, sem interseções volumétricas indevidas entre corpos. Contatos tangentes entre materiais são permitidos. O DRC das três placas tem **zero erros e zero itens desconectados**. Permanecem respectivamente 203, 20 e 36 avisos de máscara aberta/ponte de máscara nas áreas RF; os relatórios completos acompanham os nativos.

A chapa planificada mede 895,398 × 100 mm, com raio interno de 2 mm e fator K assumido de 0,4. Confirmar o raio, ferramental, ajuste dos conectores e vedação antes de fabricação. A planificação é preliminar, não uma liberação industrial.

No histórico R00 foram usados seis passes e ΔS ≤0,02. A revisão R04 foi inicialmente limitada a quatro passes e continuada somente por mais dois mediante novo pedido, com 14 núcleos, sem sweep. O alvo de referência continua 0,04; o ΔS final de 0,110424 não o atende. Atingir o limite de passes não comprova convergência. Os nativos R00 preservam as antigas varreduras; sua existência não autoriza executá-las nesta etapa. Para o estudo futuro da rede separada, a matriz S64 da antena e S10/S18 das distribuidoras serão conectadas por linhas ideais de fase, sem atenuação, com referência à potência incidente em cada entrada MIMO individual.

Para a meta original MIMO, fora desta etapa central, ainda faltam a convergência EM, matrizes e campos nas 17 frequências, circuito carregado, VSWR por entrada, ganho e H/V por canal, isolamento/correlação MIMO e ajustes de casamento. O curto DC deverá incorporar as duas bobinas de entrada da referência P1H, com nova conferência da sua integração. Os avisos de máscara, terminais soldados, conectores e chicote precisam entrar na revisão de fabricação. **Nenhum resultado R00 demonstra ainda 21 dBi em toda a banda.**

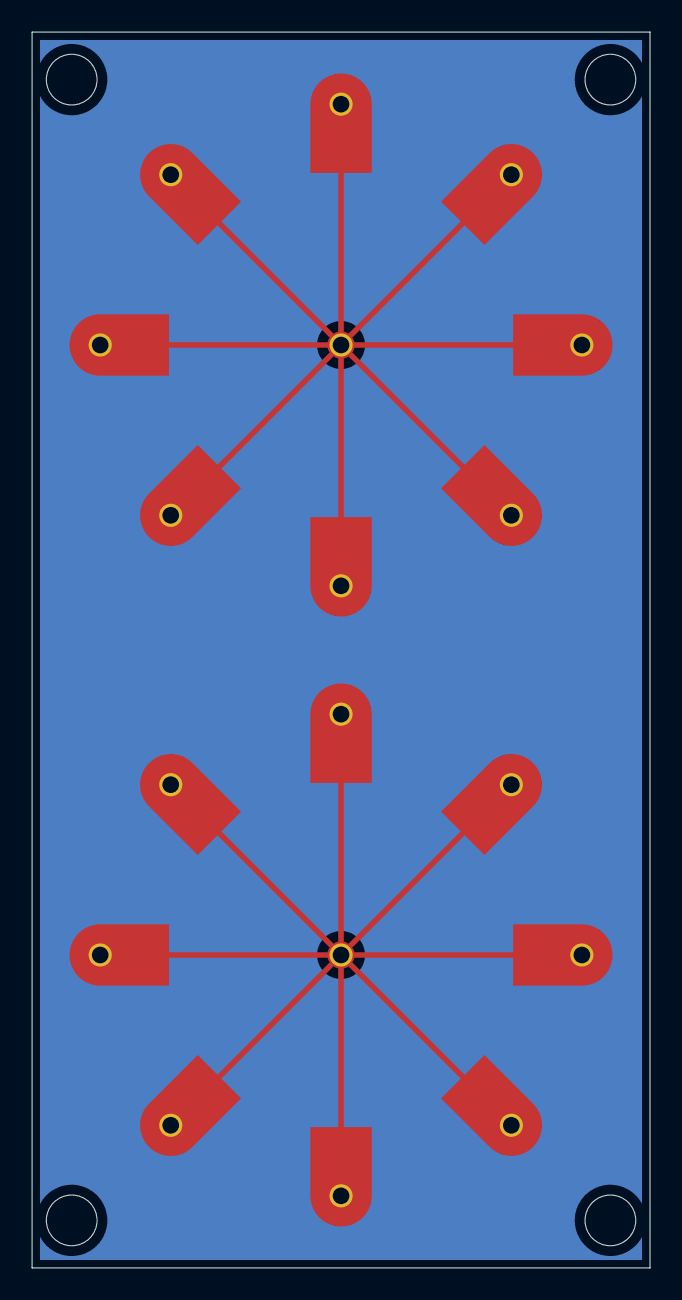
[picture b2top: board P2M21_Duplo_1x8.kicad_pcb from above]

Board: 2 copper layers, 39.0 x 78.0 mm, 22 parts (0 on the bottom side), 3 nets, no tracks yet.

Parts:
H1: H1
H2: H2
H3: H3
H4: H4
J1: J1
J2: J2
J3: J3
J4: J4
J5: J5
J6: J6
J7: J7
J8: J8
J9: J9
J10: J10
J11: J11
J12: J12
J13: J13
J14: J14
J15: J15
J16: J16
J17: J17
J18: J18

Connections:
A: J1.1, J2.1, J3.1, J4.1, J5.1, J6.1, J7.1, J8.1, J9.1
B: J10.1, J11.1, J12.1, J13.1, J14.1, J15.1, J16.1, J17.1, J18.1
GND: J1.2, J2.2, J3.2, J4.2, J5.2, J6.2, J7.2, J8.2, J9.2, J10.2, J11.2, J12.2, J13.2, J14.2, J15.2, J16.2, J17.2, J18.2

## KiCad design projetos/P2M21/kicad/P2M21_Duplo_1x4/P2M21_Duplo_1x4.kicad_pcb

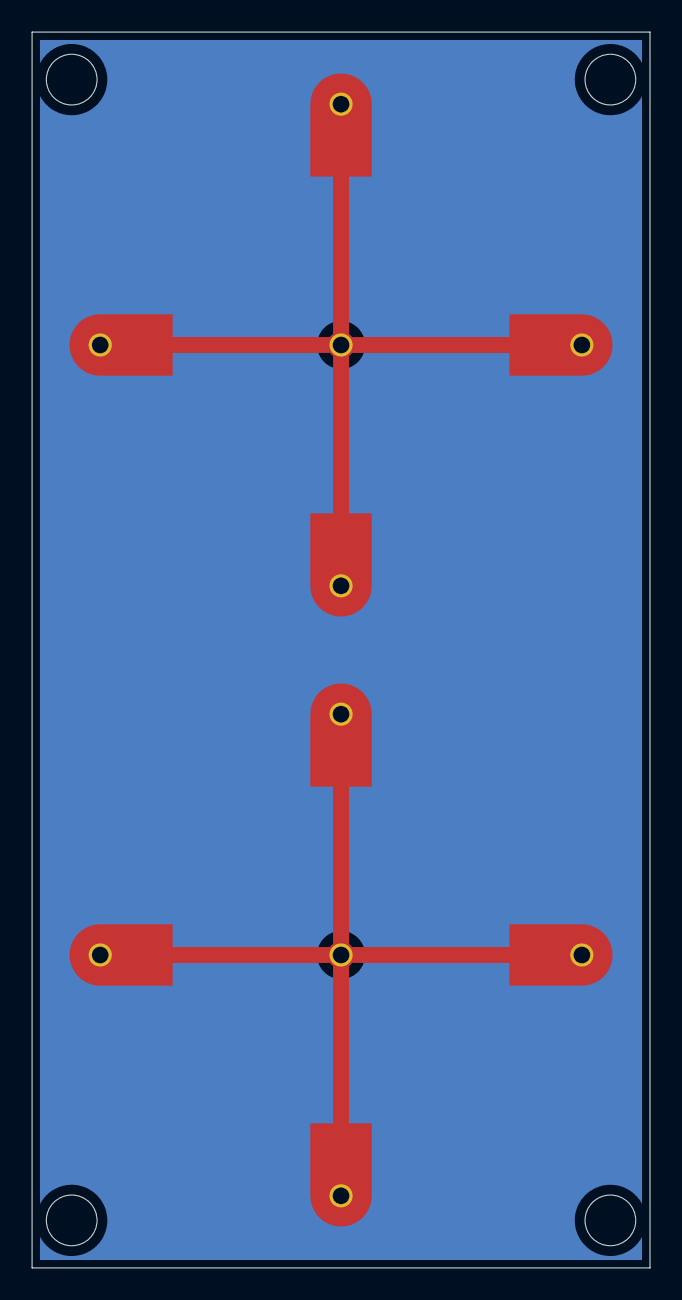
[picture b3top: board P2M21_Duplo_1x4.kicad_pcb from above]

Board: 2 copper layers, 39.0 x 78.0 mm, 14 parts (0 on the bottom side), 3 nets, no tracks yet.

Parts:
H1: H1
H2: H2
H3: H3
H4: H4
J1: J1
J2: J2
J3: J3
J4: J4
J5: J5
J6: J6
J7: J7
J8: J8
J9: J9
J10: J10

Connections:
A: J1.1, J2.1, J3.1, J4.1, J5.1
B: J6.1, J7.1, J8.1, J9.1, J10.1
GND: J1.2, J2.2, J3.2, J4.2, J5.2, J6.2, J7.2, J8.2, J9.2, J10.2

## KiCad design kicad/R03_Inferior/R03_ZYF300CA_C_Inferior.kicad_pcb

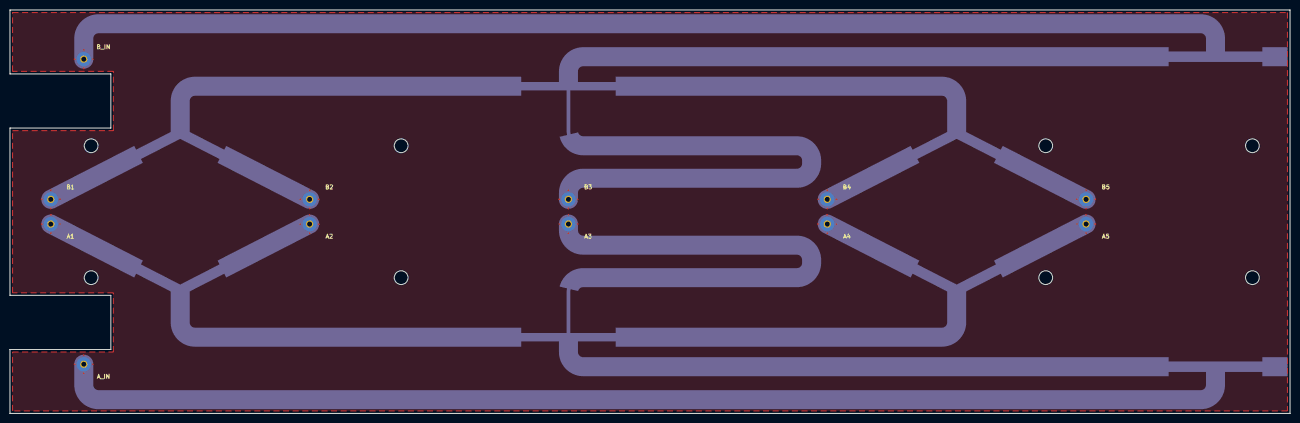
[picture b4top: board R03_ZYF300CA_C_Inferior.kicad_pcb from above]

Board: 2 copper layers, 260.1 x 82.0 mm, 20 parts (0 on the bottom side), 3 nets, no tracks yet.

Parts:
H1, H2, H3, H4, H5, H6, H7, H8: Fixacao_M2.5
J1: A_IN_UT141C
J2: A1_UT141C
J3: A2_UT141C
J4: A3_UT141C
J5: A4_UT141C
J6: A5_UT141C
J7: B_IN_UT141C
J8: B1_UT141C
J9: B2_UT141C
J10: B3_UT141C
J11: B4_UT141C
J12: B5_UT141C

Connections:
GND: J1.2, J2.2, J3.2, J4.2, J5.2, J6.2, J7.2, J8.2, J9.2, J10.2, J11.2, J12.2
POL_A: J1.1, J2.1, J3.1, J4.1, J5.1, J6.1
POL_B: J7.1, J8.1, J9.1, J10.1, J11.1, J12.1
